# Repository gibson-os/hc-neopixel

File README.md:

### Commands
| Number | Description             |
|--------|-------------------------|
| 0      | Set LEDs                |
| 1      | LED counts              |
| 2      | Write channel           |
| 4      | Blink color             |
| 5      | Reset time              |
| 10     | Start sequence          |
| 11     | Pause sequence          |
| 12     | Stop sequence           |
| 13     | Sequence EEPROM address |
| 14     | New sequence            |
| 15     | Add sequence step       |

Basic commands: [Module readme](src/hc-module/README.md)

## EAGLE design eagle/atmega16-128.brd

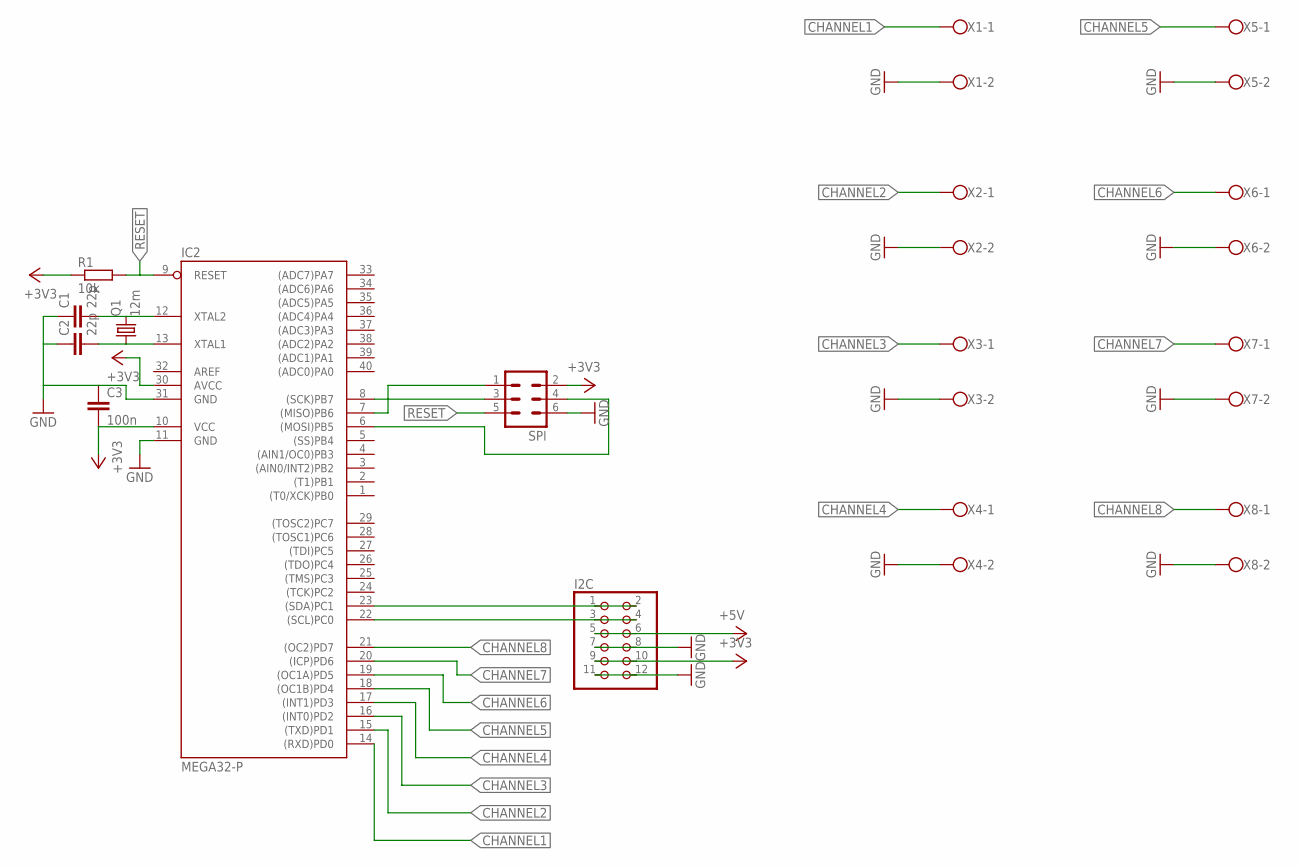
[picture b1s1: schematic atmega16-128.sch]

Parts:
C1, C2: 22p; C025-025X050
C3: 100n; C025-025X050
I2C: PINHD-2X6; 2X06
IC2: MEGA32-P; DIL40
Q1: 12m; HC49/S
R1: 10k; 0207/10
SPI: ML6
X1, X2, X3, X4, X5, X6, X7, X8: W237-102

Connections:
+3V3: C3.2, I2C.9, I2C.10, IC2.10 (VCC), IC2.30 (AVCC), R1.1, SPI.2
+5V: I2C.5, I2C.6
CHANNEL1: IC2.14 ((RXD)PD0), X1.1
CHANNEL2: IC2.15 ((TXD)PD1), X2.1
CHANNEL3: IC2.16 ((INT0)PD2), X3.1
CHANNEL4: IC2.17 ((INT1)PD3), X4.1
CHANNEL5: IC2.18 ((OC1B)PD4), X5.1
CHANNEL6: IC2.19 ((OC1A)PD5), X6.1
CHANNEL7: IC2.20 ((ICP)PD6), X7.1
CHANNEL8: IC2.21 ((OC2)PD7), X8.1
GND: C1.1, C2.1, C3.1, I2C.7, I2C.8, I2C.11, I2C.12, IC2.11 (GND), IC2.31 (GND), SPI.6, X1.2, X2.2, X3.2, X4.2, X5.2, X6.2, X7.2, X8.2
IO14: IC2.6 ((MOSI)PB5), SPI.4
unnamed: IC2.8 ((SCK)PB7), SPI.3
unnamed: IC2.7 ((MISO)PB6), SPI.1
RESET: IC2.9 (RESET), R1.2, SPI.5
SCL: I2C.3, I2C.4, IC2.22 ((SCL)PC0)
SDA: I2C.1, I2C.2, IC2.23 ((SDA)PC1)
XTAL1: C2.2, IC2.13 (XTAL1), Q1.1
XTAL2: C1.2, IC2.12 (XTAL2), Q1.2

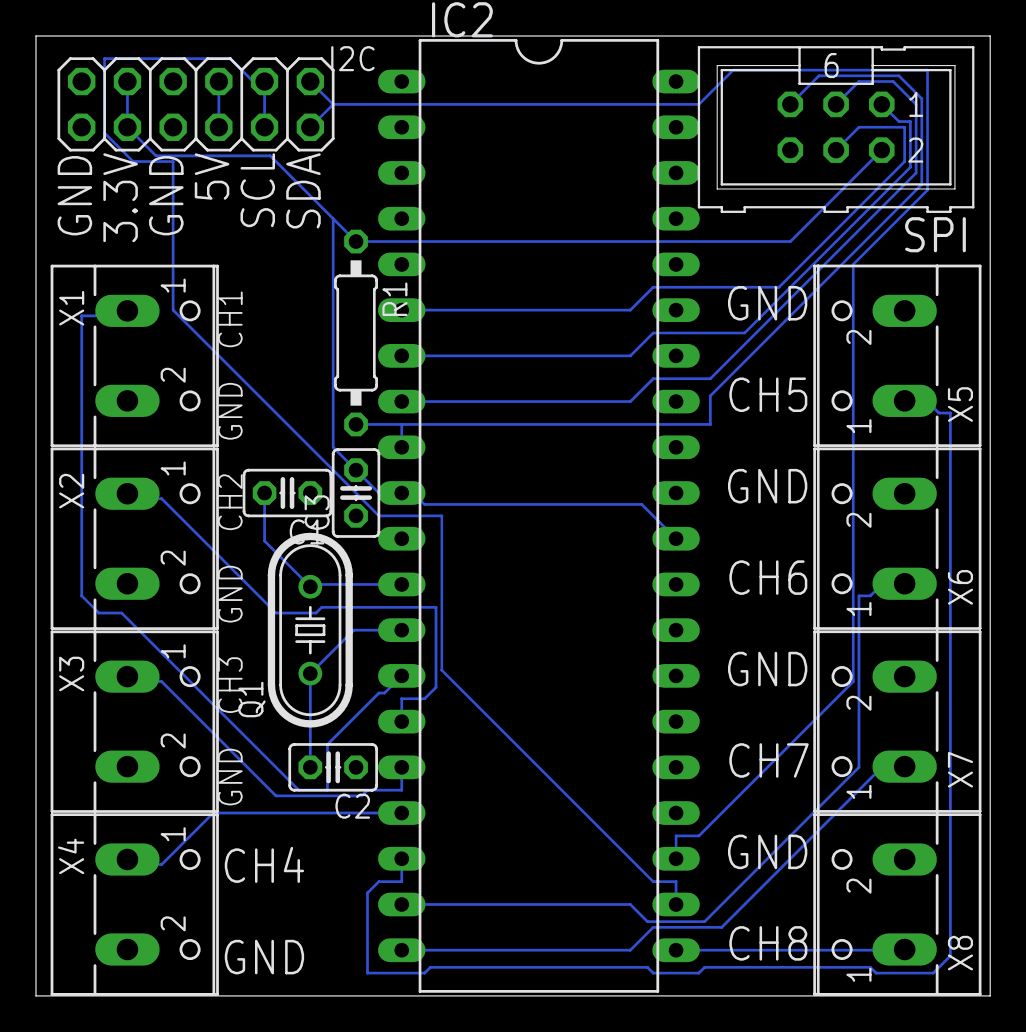
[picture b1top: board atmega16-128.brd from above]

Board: 2 copper layers, 53.0 x 53.3 mm, 16 parts (0 on the bottom side), 19 nets.

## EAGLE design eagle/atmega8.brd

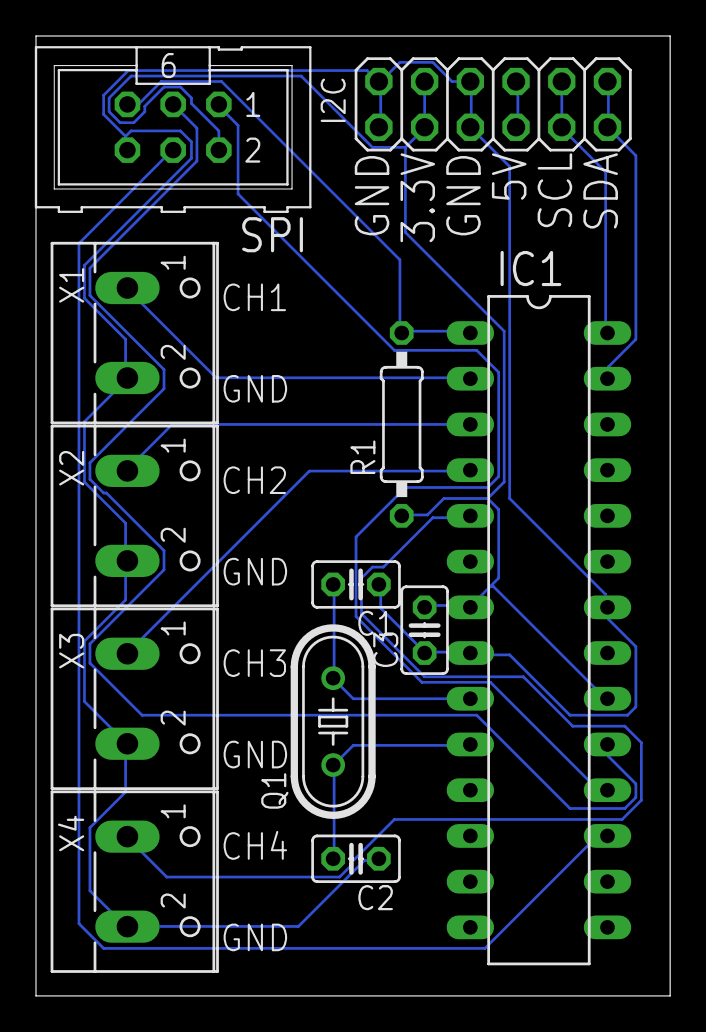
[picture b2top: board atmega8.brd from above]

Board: 2 copper layers, 35.2 x 53.3 mm, 12 parts (0 on the bottom side), 15 nets.

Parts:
C1, C2: 22p; C025-025X050
C3: 100n; C025-025X050
I2C: 2X06
IC1: MEGA8-P; DIL28-3
Q1: 12m; HC49/S
R1: 10k; 0207/10
SPI: ML6
X1, X2, X3, X4: W237-102

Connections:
+3V3: C3.2, I2C.9, I2C.10, IC1.7, IC1.20, R1.1, SPI.2
+5V: I2C.5, I2C.6
CHANNEL1: IC1.2, X1.1
CHANNEL2: IC1.3, X2.1
CHANNEL3: IC1.4, X3.1
CHANNEL4: IC1.5, X4.1
GND: C1.1, C2.1, C3.1, I2C.7, I2C.8, I2C.11, I2C.12, IC1.8, IC1.22, SPI.6, X1.2, X2.2, X3.2, X4.2
IO13: IC1.18, SPI.1
IO14: IC1.17, SPI.4
unnamed: C2.2, IC1.10, Q1.1
unnamed: C1.2, IC1.9, Q1.2
unnamed: IC1.19, SPI.3
RESET: IC1.1, R1.2, SPI.5
SCL: I2C.3, I2C.4, IC1.28
SDA: I2C.1, I2C.2, IC1.27

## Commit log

2022-12-18 Init commit
2022-12-18 Fix microchip studio project
2022-12-18 Remove ignored files
